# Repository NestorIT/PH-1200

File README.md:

# ON/OFF Automation System for a Uninterruptible Power Supply (UPS): Adding schedule function

This Arduino project was connected to a UPS to power on/off with RTC alarms (its purpose is to extend battery life). In addition, the schedule and shutdown times may also be configured by a HMI via USB port.

## Features
- Isolated voltage sensor.
- Configurable RTC DS3231 alarms (schedule - hour, minute and day of week).
- Audible alarm when UPS inverter is working (main supply has failed).
- Alarm reset button.
- HMI communication via USB port.

## IMPORTANT
**This new version has not been tested yet, however, it was based on a tested and functional one.**

## Credits
DS3231 Arduino library - [jarzebski/Arduino-DS3231](https://github.com/jarzebski/Arduino-DS3231)\
Isolated communication circuit - [pepaslabs/6N137-TTL-Serial-Optoisolator](https://github.com/pepaslabs/6N137-TTL-Serial-Optoisolator)\
Teardrops KiCad script - [NilujePerchut/kicad_scripts](https://github.com/NilujePerchut/kicad_scripts)

## License
This project is licensed under a [GNU General Public License v3.0](https://www.gnu.org/licenses/gpl-3.0.html) by [Engr. Alfredo Morales](https://www.linkedin.com/in/alfredo-morales-0a434a149/).

## Contact
alfredomorales20@gmail.com\
[Linkedin](https://www.linkedin.com/in/alfredo-morales-0a434a149/)

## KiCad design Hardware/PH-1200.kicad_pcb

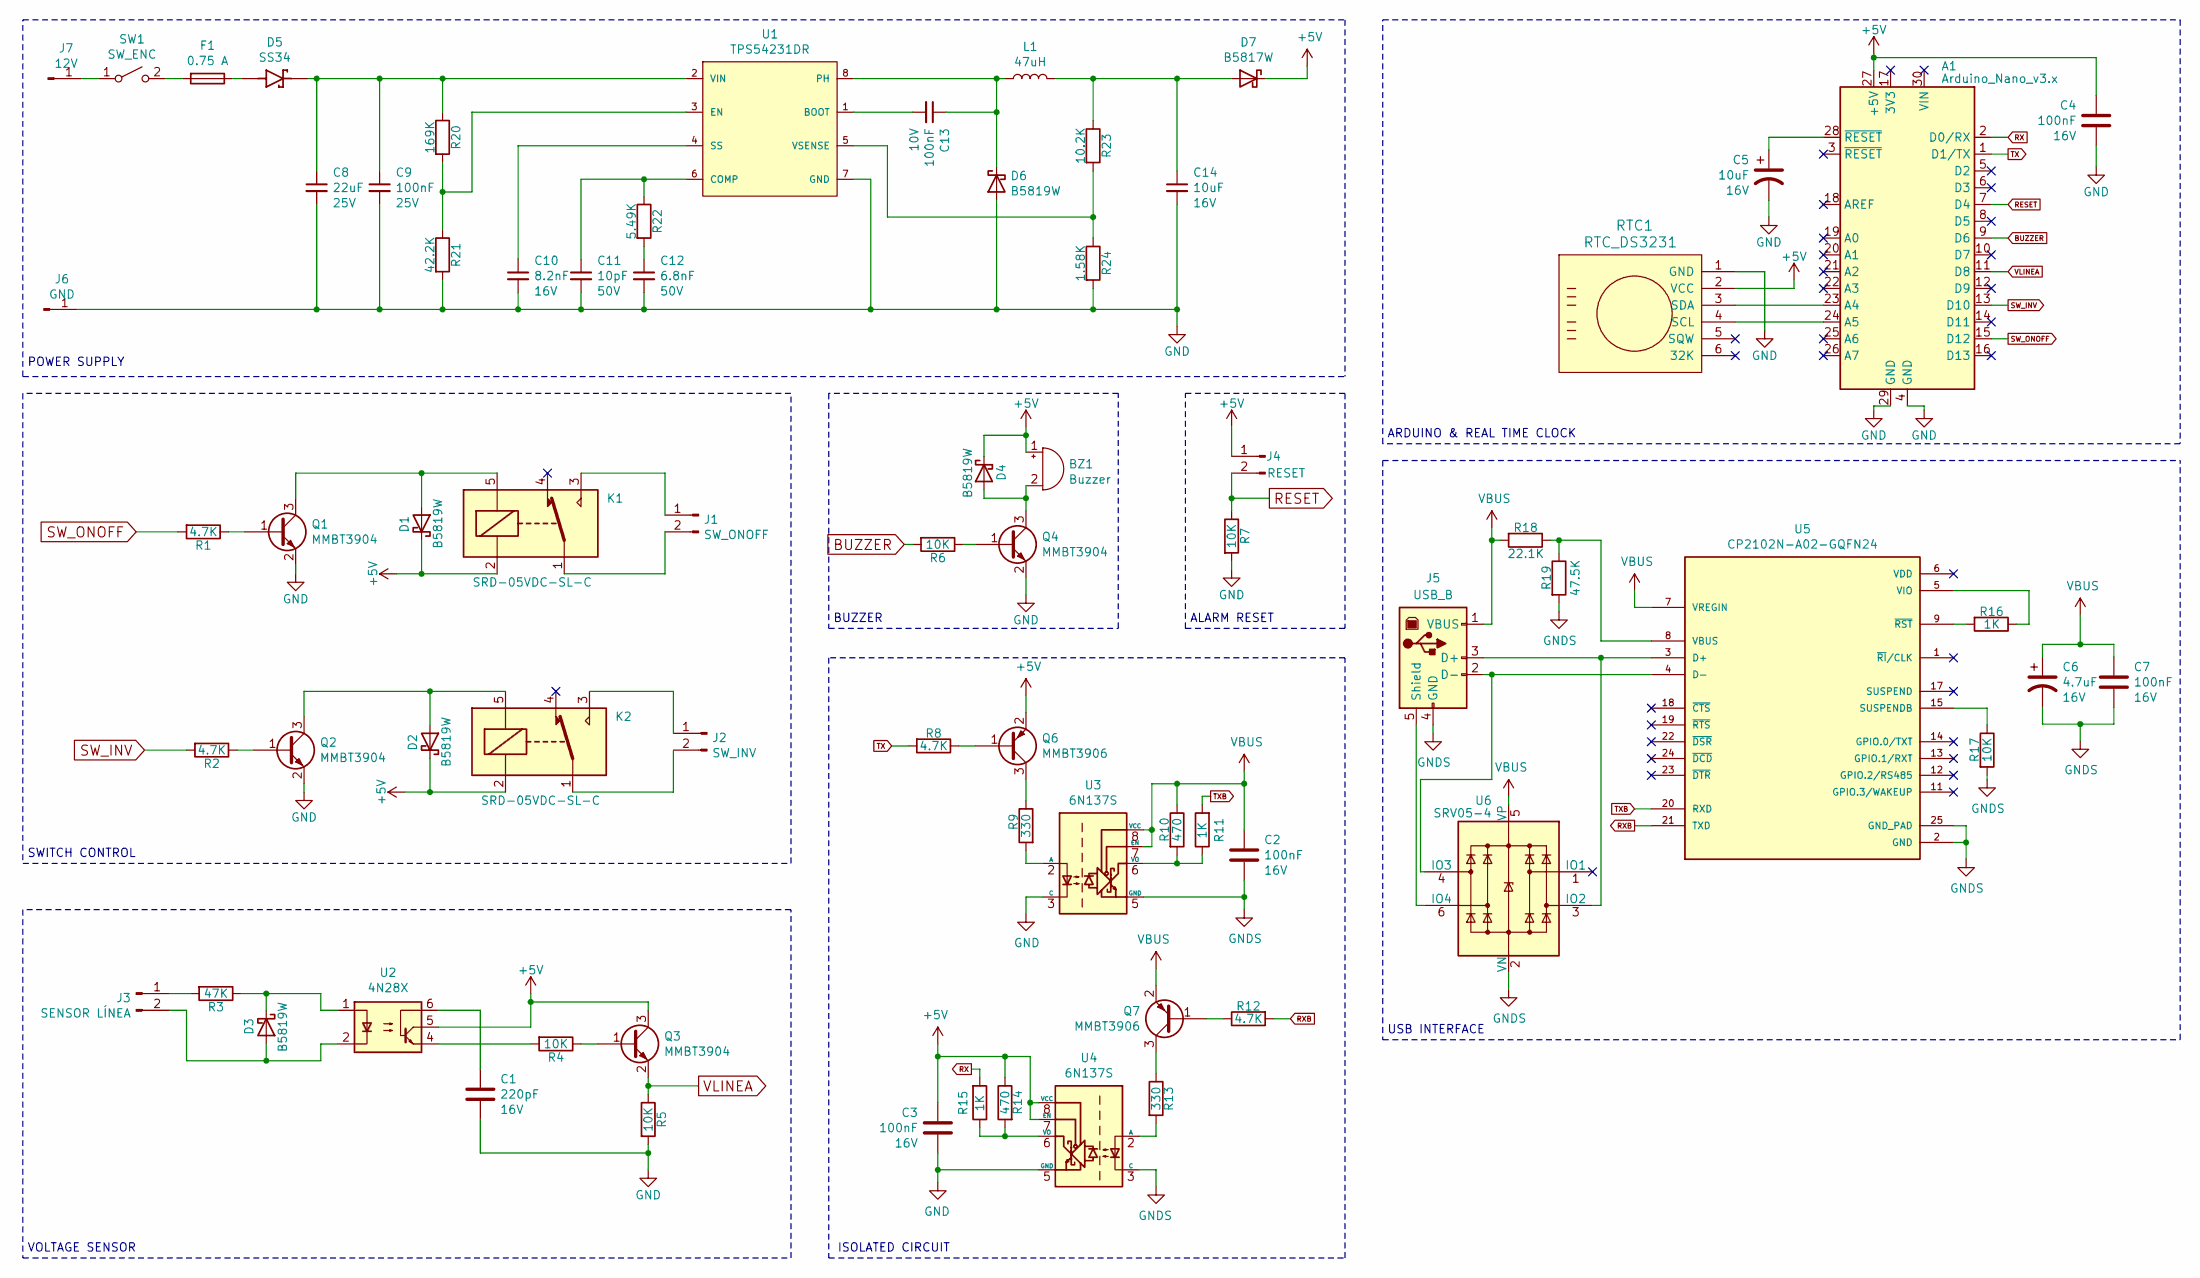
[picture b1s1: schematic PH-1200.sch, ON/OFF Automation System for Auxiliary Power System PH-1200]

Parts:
A1: Arduino_Nano_v3.x; Arduino_Nano
BZ1: Buzzer; Buzzer_12x9.5RM7.6
C1: 220pF; C_0603_1608Metric; Voltage 16V
C2, C3, C4, C7: 100nF; C_0603_1608Metric; Voltage 16V
C5: 10uF; CP_EIA-2012-12_Kemet-R; Voltage 16V
C6: 4.7uF; CP_EIA-2012-12_Kemet-R; Voltage 16V
C8: 22uF; C_1210_3225Metric; Voltage 25V
C9: 100nF; C_0402_1005Metric; Voltage 25V
C10: 8.2nF; C_0402_1005Metric; Voltage 16V
C11: 10pF; C_0402_1005Metric; Voltage 50V
C12: 6.8nF; C_0402_1005Metric; Voltage 50V
C13: 100nF; C_0402_1005Metric; Voltage 10V
C14: 10uF; C_1206_3216Metric; Voltage 16V
D1, D2, D3, D4, D6: B5819W; D_SOD-123
D5: SS34; D_SMB; PARTREV 31 Aug 2016
D7: B5817W; D_SOD-123
F1: 0.75 A; Fuse_1206_3216Metric; Part C1Q 750
J1: SW_ONOFF; TerminalBlock_Phoenix_MKDS-1,5-2_1x02_P5.00mm_Horizontal
J2: SW_INV; TerminalBlock_Phoenix_MKDS-1,5-2_1x02_P5.00mm_Horizontal
J3: SENSOR LÍNEA; PinHeader_1x02_P2.54mm_Vertical
J4: RESET; PinHeader_1x02_P2.54mm_Vertical
J5: USB_B; USB_B_OST_USB-B1HSxx_Horizontal
J6: GND; MountingHole_4mm_Pad
J7: 12V; PinHeader_1x01_P2.54mm_Vertical
K1, K2: SRD-05VDC-SL-C; Relay_SPDT_SANYOU_SRD_Series_Form_C
L1: 47uH; L_10.4x10.4_H4.8; Part B82464G4473M
Q1, Q2, Q3, Q4: MMBT3904; SOT-23
Q6, Q7: MMBT3906; SOT-23
R1, R2, R8, R12: 4.7K; R_0603_1608Metric
R3: 47K; R_0603_1608Metric
R4, R5, R6, R7, R17: 10K; R_0603_1608Metric
R9, R13: 330; R_0603_1608Metric
R10, R14: 470; R_0603_1608Metric
R11, R15, R16: 1K; R_0603_1608Metric
R18: 22.1K; R_0603_1608Metric
R19: 47.5K; R_0603_1608Metric
R20: 169K; R_0603_1608Metric
R21: 42.2K; R_0603_1608Metric
R22: 5.49K; R_0603_1608Metric
R23: 10.2K; R_0603_1608Metric
R24: 1.58K; R_0603_1608Metric
RTC1: RTC_DS3231; PinSocket_1x06_P2.54mm_Horizontal_Right
SW1: SW_ENC; PinHeader_1x02_P2.54mm_Vertical
U1: TPS54231DR; SOIC-8_3.9x4.9mm_P1.27mm; Rating Catalog
U2: 4N28X; SMDIP-6_W9.53mm
U3, U4: 6N137S; SMDIP-8_W9.53mm
U5: CP2102N-A02-GQFN24; QFN-24-1EP_4x4mm_P0.5mm_EP2.6x2.6mm_ThermalVias; PARTREV 1.3
U6: SRV05-4; SOT-23-6

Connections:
+5V: A1.27 (+5V), BZ1.1 (-), C3.1, C4.1, D1.1 (K), D2.1 (K), D4.1 (K), D7.1 (K), J4.1, K1.2, K2.2, Q3.3 (C), Q6.2 (E), R14.1, RTC1.2 (VCC), U2.5, U4.7 (EN), U4.8 (VCC)
BUZZER: A1.9 (D6), R6.2
GND: A1.4 (GND), A1.29 (GND), C1.2, C3.2, C4.2, C5.2, C8.2, C9.2, C10.2, C11.2, C12.2, C14.2, D6.2 (A), J6.1, Q1.2 (E), Q2.2 (E), Q4.2 (E), R5.2, R7.2, R21.2, R24.2, RTC1.1 (GND), U1.7 (GND), U3.3 (C), U4.5 (GND)
GNDS: C2.2, C6.2, C7.2, J5.4 (GND), R17.2, R19.2, U3.5 (GND), U4.3 (C), U5.2 (GND), U5.25 (GND_PAD), U6.2 (VN)
unnamed: A1.23 (A4), RTC1.3 (SDA)
unnamed: A1.24 (A5), RTC1.4 (SCL)
unnamed: A1.28 (~RESET), C5.1
unnamed: BZ1.2 (+), D4.2 (A), Q4.3 (C)
unnamed: C1.1, U2.6
unnamed: C8.1, C9.1, D5.1 (K), R20.1, U1.2 (VIN)
unnamed: C10.1, U1.4 (SS)
unnamed: C11.1, R22.1, U1.6 (COMP)
unnamed: C12.1, R22.2
unnamed: C13.1, D6.1 (K), L1.1, U1.8 (PH)
unnamed: C13.2, U1.1 (BOOT)
unnamed: C14.1, D7.2 (A), L1.2, R23.1
unnamed: D1.2 (A), K1.5, Q1.3 (C)
unnamed: D2.2 (A), K2.5, Q2.3 (C)
unnamed: D3.1 (K), R3.1, U2.1
unnamed: D3.2 (A), J3.2, U2.2
unnamed: D5.2 (A), F1.1
unnamed: F1.2, SW1.2 (B)
unnamed: J1.1, K1.3
unnamed: J1.2, K1.1
unnamed: J2.1, K2.3
unnamed: J2.2, K2.1
unnamed: J3.1, R3.2
unnamed: J5.2 (D-), U5.4 (D-), U6.4 (IO3)
unnamed: J5.3 (D+), U5.3 (D+), U6.3 (IO2)
unnamed: J5.5 (Shield), U6.6 (IO4)
unnamed: J7.1, SW1.1 (A)
unnamed: Q1.1 (B), R1.1
unnamed: Q2.1 (B), R2.1
unnamed: Q3.1 (B), R4.1
unnamed: Q4.1 (B), R6.1
unnamed: Q6.1 (B), R8.1
unnamed: Q6.3 (C), R9.1
unnamed: Q7.1 (B), R12.1
unnamed: Q7.3 (C), R13.1
unnamed: R4.2, U2.4
unnamed: R9.2, U3.2 (A)
unnamed: R10.2, R11.1, U3.6 (VO)
unnamed: R13.2, U4.2 (A)
unnamed: R14.2, R15.1, U4.6 (VO)
unnamed: R16.1, U5.5 (VIO)
unnamed: R16.2, U5.9 (~RST)
unnamed: R17.1, U5.15 (SUSPENDB)
unnamed: R18.1, R19.1, U5.8 (VBUS)
unnamed: R20.2, R21.1, U1.3 (EN)
unnamed: R23.2, R24.1, U1.5 (VSENSE)
RESET: A1.7 (D4), J4.2, R7.1
RX: A1.2 (D0/RX), R15.2
RXB: R12.2, U5.21 (TXD)
SW_INV: A1.13 (D10), R2.2
SW_ONOFF: A1.15 (D12), R1.2
TX: A1.1 (D1/TX), R8.2
TXB: R11.2, U5.20 (RXD)
VBUS: C2.1, C6.1, C7.1, J5.1 (VBUS), Q7.2 (E), R10.1, R18.2, U3.7 (EN), U3.8 (VCC), U5.7 (VREGIN), U6.5 (VP)
VLINEA: A1.11 (D8), Q3.2 (E), R5.1

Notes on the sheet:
SWITCH CONTROL
VOLTAGE SENSOR
BUZZER
ALARM RESET
ISOLATED CIRCUIT
USB INTERFACE
ARDUINO & REAL TIME CLOCK
POWER SUPPLY

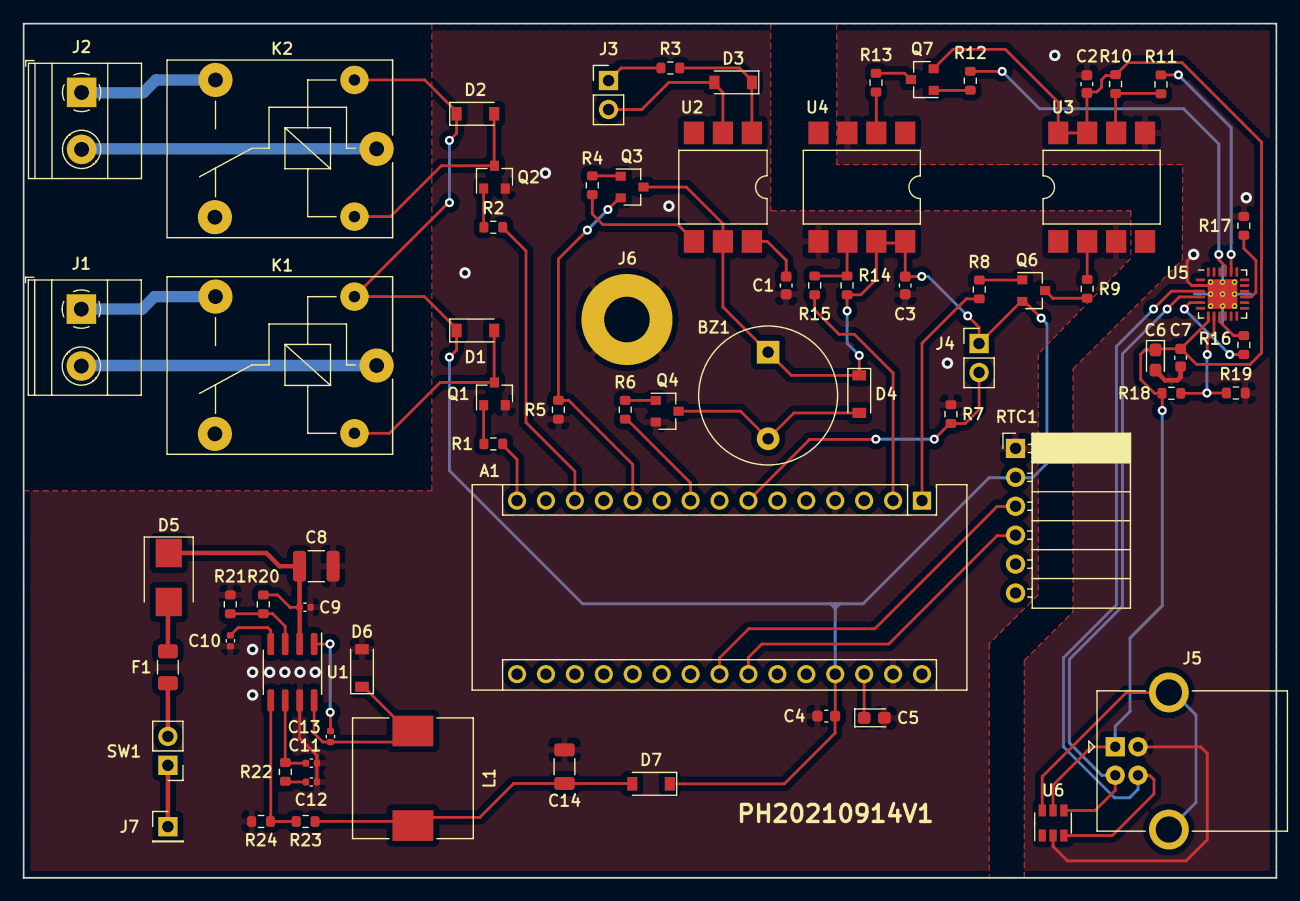
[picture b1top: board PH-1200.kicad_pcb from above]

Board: 2 copper layers, 110.0 x 75.0 mm, 72 parts (0 on the bottom side), 59 nets.

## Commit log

2021-09-08 Add KiCad files
2021-09-08 Add schematic file
2021-09-08 Add 3D images
2021-09-08 Add Arduino Nano V3 datasheet
2021-09-14 Update KiCad files
2021-09-14 Update 3D files
2022-12-12 Add RFC 9271
    Add RFC 9271: Uninterruptible Power Supply Management Protocol Commands and Responses
